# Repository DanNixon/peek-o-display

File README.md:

# Peek-o-Display

The moderately simple coming together of a Pi Pico (compatible) and generic 2.8" display with touch panel and SD card slot.
Designed to be a simple module that can slot onto various pieces of hardware that need a microcontroller and display (and maybe storage).

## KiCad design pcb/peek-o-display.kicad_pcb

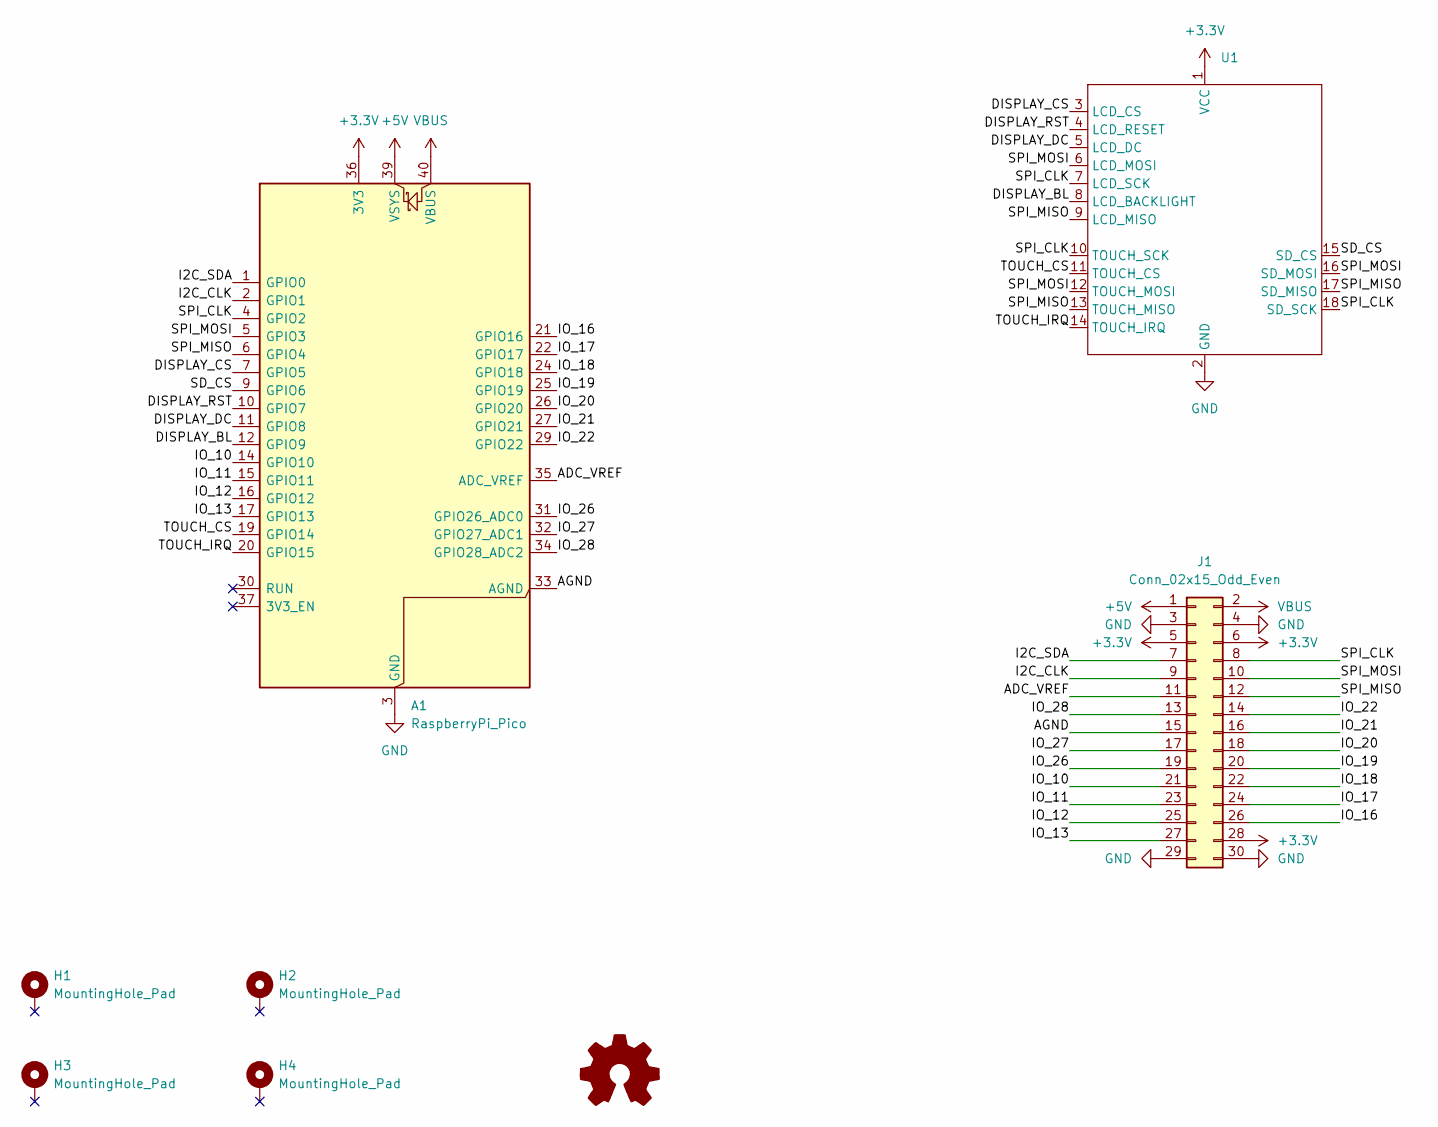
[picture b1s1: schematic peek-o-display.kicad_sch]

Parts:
A1: RaspberryPi_Pico; RaspberryPi_Pico_Common
H1, H2, H3, H4: MountingHole_Pad; MountingHole_3.2mm_M3_Pad_Via
J1: Conn_02x15_Odd_Even; PinSocket_2x15_P2.54mm_Vertical
U1: ILI9341_2.8in_with_touch_and_sd

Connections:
+3.3V: A1.36 (3V3), J1.5, J1.6, J1.28, U1.1 (VCC)
+5V: A1.39 (VSYS), J1.1
/ADC_VREF: A1.35 (ADC_VREF), J1.11
/AGND: A1.33 (AGND), J1.15
/DISPLAY_BL: A1.12 (GPIO9), U1.8 (LCD_BACKLIGHT)
/DISPLAY_CS: A1.7 (GPIO5), U1.3 (LCD_CS)
/DISPLAY_DC: A1.11 (GPIO8), U1.5 (LCD_DC)
/DISPLAY_RST: A1.10 (GPIO7), U1.4 (LCD_RESET)
/I2C_CLK: A1.2 (GPIO1), J1.9
/I2C_SDA: A1.1 (GPIO0), J1.7
/IO_10: A1.14 (GPIO10), J1.21
/IO_11: A1.15 (GPIO11), J1.23
/IO_12: A1.16 (GPIO12), J1.25
/IO_13: A1.17 (GPIO13), J1.27
/IO_16: A1.21 (GPIO16), J1.26
/IO_17: A1.22 (GPIO17), J1.24
/IO_18: A1.24 (GPIO18), J1.22
/IO_19: A1.25 (GPIO19), J1.20
/IO_20: A1.26 (GPIO20), J1.18
/IO_21: A1.27 (GPIO21), J1.16
/IO_22: A1.29 (GPIO22), J1.14
/IO_26: A1.31 (GPIO26_ADC0), J1.19
/IO_27: A1.32 (GPIO27_ADC1), J1.17
/IO_28: A1.34 (GPIO28_ADC2), J1.13
/SD_CS: A1.9 (GPIO6), U1.15 (SD_CS)
/SPI_CLK: A1.4 (GPIO2), J1.8, U1.7 (LCD_SCK), U1.10 (TOUCH_SCK), U1.18 (SD_SCK)
/SPI_MISO: A1.6 (GPIO4), J1.12, U1.9 (LCD_MISO), U1.13 (TOUCH_MISO), U1.17 (SD_MISO)
/SPI_MOSI: A1.5 (GPIO3), J1.10, U1.6 (LCD_MOSI), U1.12 (TOUCH_MOSI), U1.16 (SD_MOSI)
/TOUCH_CS: A1.19 (GPIO14), U1.11 (TOUCH_CS)
/TOUCH_IRQ: A1.20 (GPIO15), U1.14 (TOUCH_IRQ)
GND: A1.3 (GND), A1.8 (GND), A1.13 (GND), A1.18 (GND), A1.23 (GND), A1.28 (GND), A1.38 (GND), J1.3, J1.4, J1.29, J1.30, U1.2 (GND)
VBUS: A1.40 (VBUS), J1.2

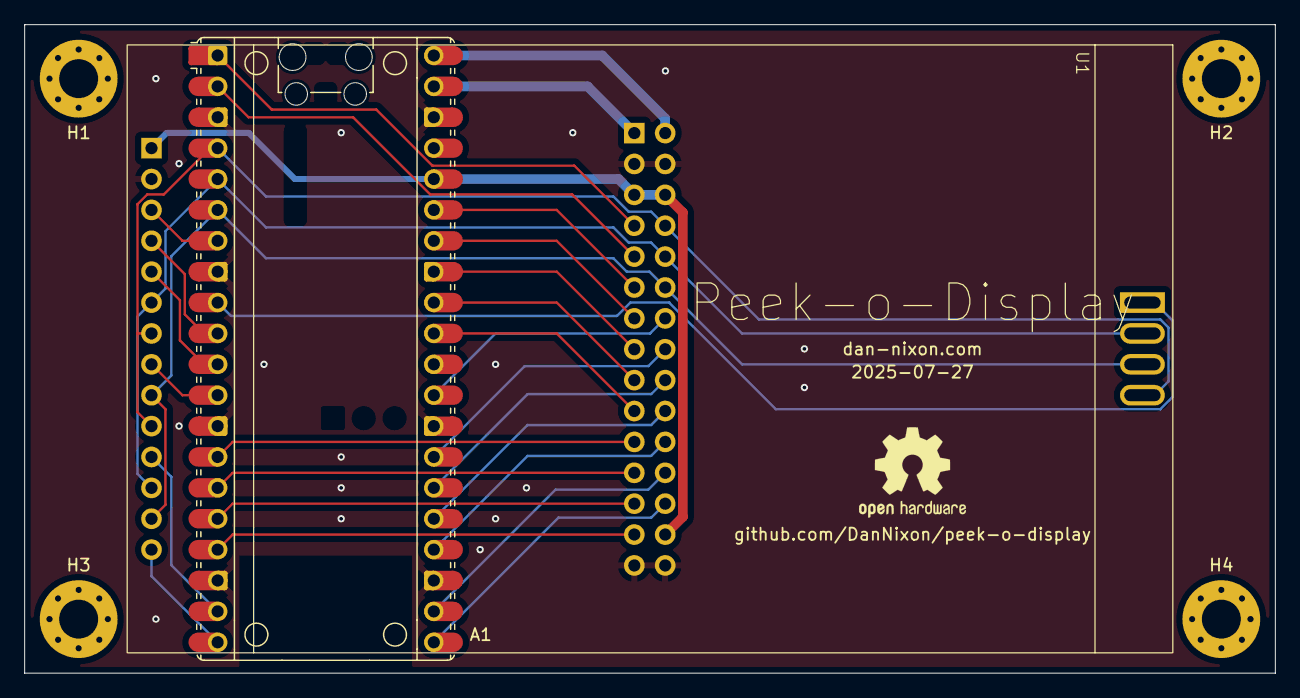
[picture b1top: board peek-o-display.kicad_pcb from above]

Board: 2 copper layers, 102.9 x 53.3 mm, 7 parts (1 on the bottom side), 32 nets.

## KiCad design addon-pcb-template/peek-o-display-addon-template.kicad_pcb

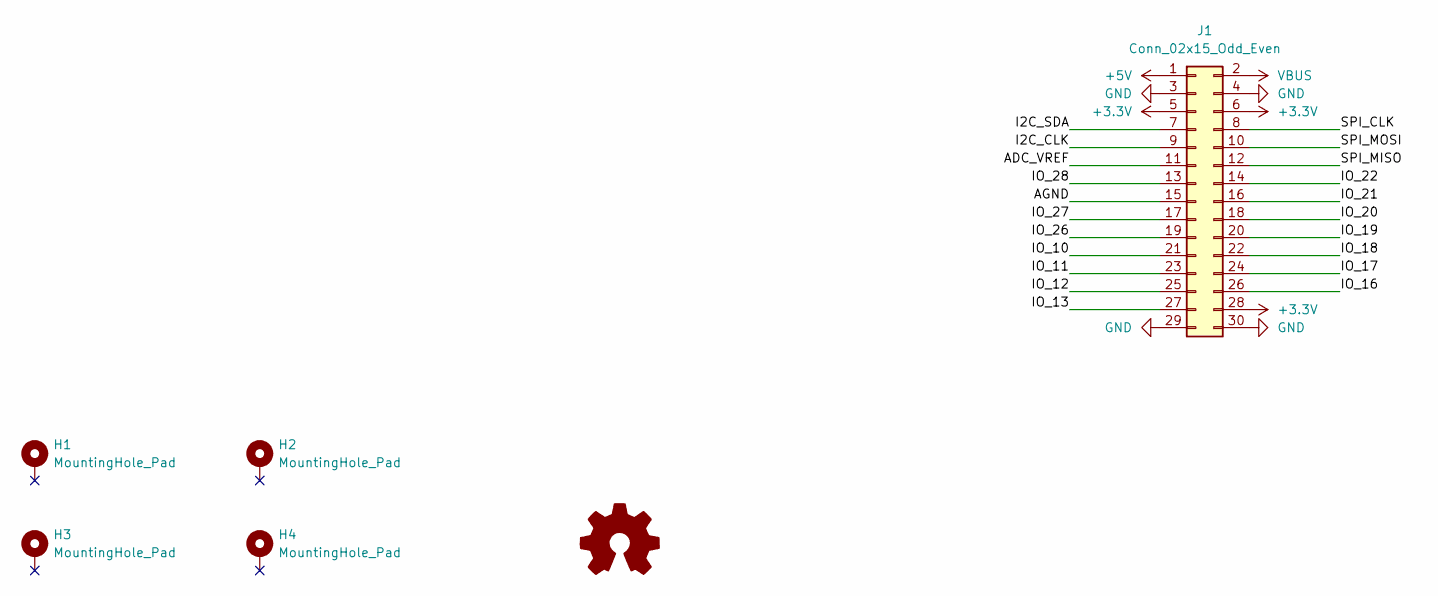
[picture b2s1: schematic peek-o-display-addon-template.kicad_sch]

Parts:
H1, H2, H3, H4: MountingHole_Pad; MountingHole_3.2mm_M3_Pad_Via
J1: Conn_02x15_Odd_Even; PinSocket_2x15_P2.54mm_Vertical

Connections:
+3.3V: J1.5, J1.6, J1.28
+5V: J1.1
/ADC_VREF: J1.11
/AGND: J1.15
/I2C_CLK: J1.9
/I2C_SDA: J1.7
/IO_10: J1.21
/IO_11: J1.23
/IO_12: J1.25
/IO_13: J1.27
/IO_16: J1.26
/IO_17: J1.24
/IO_18: J1.22
/IO_19: J1.20
/IO_20: J1.18
/IO_21: J1.16
/IO_22: J1.14
/IO_26: J1.19
/IO_27: J1.17
/IO_28: J1.13
/SPI_CLK: J1.8
/SPI_MISO: J1.12
/SPI_MOSI: J1.10
GND: J1.3, J1.4, J1.29, J1.30
VBUS: J1.2

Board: 2 copper layers, 5 parts (1 on the bottom side), 2 nets, no tracks yet.

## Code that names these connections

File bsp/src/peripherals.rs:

// Non renamed re-exported peripherals
pub use embassy_rp::peripherals::{
    ADC, ADC_TEMP_SENSOR, BOOTSEL, CORE1, DMA_CH0, DMA_CH1, DMA_CH2, DMA_CH3, DMA_CH4, DMA_CH5,
    DMA_CH6, DMA_CH7, DMA_CH8, DMA_CH9, DMA_CH10, DMA_CH11, FLASH, I2C0, I2C1, PIN_0, PIN_1,
    PIN_10, PIN_11, PIN_12, PIN_13, PIN_16, PIN_17, PIN_18, PIN_19, PIN_20, PIN_21, PIN_22, PIN_23,
    PIN_24, PIN_25, PIN_26, PIN_27, PIN_28, PIN_29, PIN_QSPI_SCLK, PIN_QSPI_SD0, PIN_QSPI_SD1,
    PIN_QSPI_SD2, PIN_QSPI_SD3, PIN_QSPI_SS, PIO0, PIO1, PWM_SLICE0, PWM_SLICE1, PWM_SLICE2,
    PWM_SLICE3, PWM_SLICE4, PWM_SLICE5, PWM_SLICE6, PWM_SLICE7, RTC, SPI0, SPI1, UART0, UART1, USB,
    WATCHDOG,
};

// Non renamed re-exported peripherals
#[cfg(feature = "rp235xa")]
pub use embassy_rp::peripherals::{
    DMA_CH12, DMA_CH13, DMA_CH14, DMA_CH15, PIO2, PWM_SLICE8, PWM_SLICE9, PWM_SLICE10, PWM_SLICE11,
    TRNG,
};

// Renamed pins
pub use embassy_rp::peripherals::{
    PIN_2 as SPI_CLK, PIN_3 as SPI_MOSI, PIN_4 as SPI_MISO, PIN_5 as DISPLAY_CS,
    PIN_6 as SDCARD_CS, PIN_7 as DISPLAY_RESET, PIN_8 as DISPLAY_DC, PIN_9 as DISPLAY_BACKLIGHT,
    PIN_14 as TOUCH_CS, PIN_15 as TOUCH_IRQ,
};

pub use embassy_rp::Peri;

/// Struct containing peripherals, appropriately named for the Peek-o-Display board.
#[allow(non_snake_case)]
pub struct Peripherals {
    pub PIN_0: Peri<'static, PIN_0>,
    pub PIN_1: Peri<'static, PIN_1>,
    pub PIN_10: Peri<'static, PIN_10>,
    pub PIN_11: Peri<'static, PIN_11>,
    pub PIN_12: Peri<'static, PIN_12>,
    pub PIN_13: Peri<'static, PIN_13>,
    pub PIN_16: Peri<'static, PIN_16>,
    pub PIN_17: Peri<'static, PIN_17>,
    pub PIN_18: Peri<'static, PIN_18>,
    pub PIN_19: Peri<'static, PIN_19>,
    pub PIN_20: Peri<'static, PIN_20>,
    pub PIN_21: Peri<'static, PIN_21>,
    pub PIN_22: Peri<'static, PIN_22>,
    pub PIN_23: Peri<'static, PIN_23>,
    pub PIN_24: Peri<'static, PIN_24>,
    pub PIN_25: Peri<'static, PIN_25>,
    pub PIN_26: Peri<'static, PIN_26>,
    pub PIN_27: Peri<'static, PIN_27>,
    pub PIN_28: Peri<'static, PIN_28>,
    pub PIN_29: Peri<'static, PIN_29>,

    pub PIN_QSPI_SCLK: Peri<'static, PIN_QSPI_SCLK>,
    pub PIN_QSPI_SS: Peri<'static, PIN_QSPI_SS>,
    pub PIN_QSPI_SD0: Peri<'static, PIN_QSPI_SD0>,
    pub PIN_QSPI_SD1: Peri<'static, PIN_QSPI_SD1>,
    pub PIN_QSPI_SD2: Peri<'static, PIN_QSPI_SD2>,
    pub PIN_QSPI_SD3: Peri<'static, PIN_QSPI_SD3>,

    pub UART0: Peri<'static, UART0>,
    pub UART1: Peri<'static, UART1>,

    pub SPI1: Peri<'static, SPI1>,

    pub I2C0: Peri<'static, I2C0>,
    pub I2C1: Peri<'static, I2C1>,

    pub DMA_CH0: Peri<'static, DMA_CH0>,
    pub DMA_CH1: Peri<'static, DMA_CH1>,
    pub DMA_CH2: Peri<'static, DMA_CH2>,
    pub DMA_CH3: Peri<'static, DMA_CH3>,
    pub DMA_CH4: Peri<'static, DMA_CH4>,
    pub DMA_CH5: Peri<'static, DMA_CH5>,
    pub DMA_CH6: Peri<'static, DMA_CH6>,
    pub DMA_CH7: Peri<'static, DMA_CH7>,
    pub DMA_CH8: Peri<'static, DMA_CH8>,
    pub DMA_CH9: Peri<'static, DMA_CH9>,
    pub DMA_CH10: Peri<'static, DMA_CH10>,
    pub DMA_CH11: Peri<'static, DMA_CH11>,
    #[cfg(feature = "rp235xa")]
    pub DMA_CH12: Peri<'static, DMA_CH12>,
    #[cfg(feature = "rp235xa")]
    pub DMA_CH13: Peri<'static, DMA_CH13>,
    #[cfg(feature = "rp235xa")]
    pub DMA_CH14: Peri<'static, DMA_CH14>,
    #[cfg(feature = "rp235xa")]
    pub DMA_CH15: Peri<'static, DMA_CH15>,

    pub PWM_SLICE0: Peri<'static, PWM_SLICE0>,
    pub PWM_SLICE1: Peri<'static, PWM_SLICE1>,
    pub PWM_SLICE2: Peri<'static, PWM_SLICE2>,
    pub PWM_SLICE3: Peri<'static, PWM_SLICE3>,
    pub PWM_SLICE4: Peri<'static, PWM_SLICE4>,
    pub PWM_SLICE5: Peri<'static, PWM_SLICE5>,
    pub PWM_SLICE6: Peri<'static, PWM_SLICE6>,
    pub PWM_SLICE7: Peri<'static, PWM_SLICE7>,
    #[cfg(feature = "rp235xa")]
    pub PWM_SLICE8: Peri<'static, PWM_SLICE8>,
    #[cfg(feature = "rp235xa")]
    pub PWM_SLICE9: Peri<'static, PWM_SLICE9>,
    #[cfg(feature = "rp235xa")]
    pub PWM_SLICE10: Peri<'static, PWM_SLICE10>,
    #[cfg(feature = "rp235xa")]
    pub PWM_SLICE11: Peri<'static, PWM_SLICE11>,

    pub USB: Peri<'static, USB>,

    pub RTC: Peri<'static, RTC>,

    pub FLASH: Peri<'static, FLASH>,

    pub ADC: Peri<'static, ADC>,
    pub ADC_TEMP_SENSOR: Peri<'static, ADC_TEMP_SENSOR>,

    pub CORE1: Peri<'static, CORE1>,

    pub PIO0: Peri<'static, PIO0>,
    pub PIO1: Peri<'static, PIO1>,
    #[cfg(feature = "rp235xa")]
    pub PIO2: Peri<'static, PIO2>,

    pub WATCHDOG: Peri<'static, WATCHDOG>,

    pub BOOTSEL: Peri<'static, BOOTSEL>,

    #[cfg(feature = "rp235xa")]
    pub TRNG: Peri<'static, TRNG>,
}

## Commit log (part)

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2025-04-28 pcb: initial version
2025-04-28 bsp: initial version
2025-04-28 bsp: examples
2025-04-28 Update devenv
2025-04-28 bsp: add kitchen sink example for Pico 2
2025-04-28 bsp: add Pico 2 copy of demo firmware
2025-04-28 bsp: tidy examples
2025-04-28 bsp: use in all examples
2025-07-21 bsp: update Rust version
2025-07-22 bsp: finish board peripheral support
2025-07-22 build(deps): update embassy-rp requirement
    Updates the requirements on [embassy-rp](https://github.com/embassy-rs/embassy) to permit the latest version.
    Updates `embassy-rp` to 0.5.0
    - [Changelog](https://github.com/embassy-rs/embassy/blob/main/RELEASE.md)
    - [Commits](https://github.com/embassy-rs/embassy/compare/embassy-rp-v0.4.0...embassy-rp-v0.5.0)
    ---
    updated-dependencies:
2025-07-22 build(deps): bump the cargo-dependencies group
    Updates the requirements on [assign-resources](https://github.com/adamgreig/assign-resources) and [embassy-rp](https://github.com/embassy-rs/embassy) to permit the latest version.
    Updates `assign-resources` to 0.5.0
    - [Changelog](https://github.com/adamgreig/assign-resources/blob/main/CHANGELOG.md)
    - [Commits](https://github.com/adamgreig/assign-resources/compare/v0.4.1...v0.5.0)
    Updates `embassy-rp` to 0.5.0
    - [Changelog](https://github.com/embassy-rs/embassy/blob/main/RELEASE.md)
2025-07-23 Add case template
2025-07-23 Finish touch screen functionality
2025-07-23 build(deps): bump the cargo-dependencies group in /bsp with 4 updates
    Updates the requirements on [embassy-embedded-hal](https://github.com/embassy-rs/embassy), [embassy-rp](https://github.com/embassy-rs/embassy), [embassy-sync](https://github.com/embassy-rs/embassy) a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
    Updates `embassy-embedded-hal` to 0.3.1
    - [Changelog](https://github.com/embassy-rs/embassy/blob/main/RELEASE.md)
    - [Commits](https://github.com/embassy-rs/embassy/compare/embassy-embedded-hal-v0.3.0...embassy-rp-v0.3.1)
    Updates `embassy-rp` to 0.6.0
    - [Changelog](https://github.com/embassy-rs/embassy/blob/main/RELE
2025-07-23 Update Cargo dependencies
2025-07-25 Add addon PCB template
2025-07-27 Slot SD card SPI holes on display module
    Addresses the fact that not all modules seem to have the same distance
    between the two banks of pin headers.
2025-08-01 build(deps): update embassy-executor requirement
    Updates the requirements on [embassy-executor](https://github.com/embassy-rs/embassy) to permit the latest version.
    Updates `embassy-executor` to 0.7.0
    - [Changelog](https://github.com/embassy-rs/embassy/blob/main/RELEASE.md)
    - [Commits](https://github.com/embassy-rs/embassy/compare/embassy-executor-v0.7.0...embassy-executor-v0.7.0)
    ---
    updated-dependencies:
2025-09-02 build(deps): bump the cargo-dependencies group
    Updates the requirements on [embassy-executor](https://github.com/embassy-rs/embassy) and [embassy-time](https://github.com/embassy-rs/embassy) to permit the latest version.
    Updates `embassy-executor` to 0.9.1
    - [Changelog](https://github.com/embassy-rs/embassy/blob/main/RELEASE.md)
    - [Commits](https://github.com/embassy-rs/embassy/compare/embassy-executor-v0.8.0...embassy-executor-v0.9.1)
    Updates `embassy-time` to 0.5.0
    - [Changelog](https://github.com/embassy-rs/embassy/blob/main/RELEASE.md)
2025-09-02 build(deps): bump actions/checkout from 4 to 5
    Bumps [actions/checkout](https://github.com/actions/checkout) from 4 to 5.
    - [Release notes](https://github.com/actions/checkout/releases)
    - [Changelog](https://github.com/actions/checkout/blob/main/CHANGELOG.md)
    - [Commits](https://github.com/actions/checkout/compare/v4...v5)
    ---
    updated-dependencies:
2025-09-07 build(deps): bump the cargo-dependencies group in /bsp with 3 updates
    Updates the requirements on [embassy-embedded-hal](https://github.com/embassy-rs/embassy), [embassy-rp](https://github.com/embassy-rs/embassy) and [embassy-time](https://github.com/embassy-rs/embassy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
    Updates `embassy-embedded-hal` to 0.5.0
    - [Changelog](https://github.com/embassy-rs/embassy/blob/main/RELEASE.md)
    - [Commits](https://github.com/embassy-rs/embassy/compare/embassy-embedded-hal-v0.4.0...embassy-embedded-hal-v0.5.0)
    Updates `embassy-rp` to 0.8.0
    - [Changelog](https://github.com/embassy-rs/embassy/blob/main/RELEASE.md)
2025-12-02 build(deps): update embassy-rp requirement
    Updates the requirements on [embassy-rp](https://github.com/embassy-rs/embassy) to permit the latest version.
    Updates `embassy-rp` to 0.9.0
    - [Changelog](https://github.com/embassy-rs/embassy/blob/main/RELEASE.md)
    - [Commits](https://github.com/embassy-rs/embassy/compare/embassy-rp-v0.8.0...embassy-rp-v0.9.0)
    ---
    updated-dependencies:
2025-12-02 build(deps): bump actions/checkout from 5 to 6
    Bumps [actions/checkout](https://github.com/actions/checkout) from 5 to 6.
    - [Release notes](https://github.com/actions/checkout/releases)
    - [Changelog](https://github.com/actions/checkout/blob/main/CHANGELOG.md)
    - [Commits](https://github.com/actions/checkout/compare/v5...v6)
    ---
    updated-dependencies:
2026-01-13 Switch to flake, update dependabot and Rust version
2026-02-14 Correct a copy-paste mistake
2026-02-14 Use rustup provided rustfmt
2026-02-14 Update flake inputs
2026-04-02 build(deps): bump DeterminateSystems/nix-installer-action from 21 to 22
    Bumps [DeterminateSystems/nix-installer-action](https://github.com/determinatesystems/nix-installer-action) from 21 to 22.
    - [Release notes](https://github.com/determinatesystems/nix-installer-action/releases)
    - [Commits](https://github.com/determinatesystems/nix-installer-action/compare/v21...v22)
    ---
    updated-dependencies:
    - dependency-name: DeterminateSystems/nix-installer-action
2026-04-05 build(deps): bump the cargo-dependencies group across 6 directories with 5 updates
    Updates the requirements on [embassy-embedded-hal](https://github.com/embassy-rs/embassy), [embassy-rp](https://github.com/embassy-rs/embassy), [embassy-sync](https://github.com/embassy-rs/embassy), 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
    Updates `embassy-embedded-hal` to 0.6.0
    - [Changelog](https://github.com/embassy-rs/embassy/blob/main/RELEASE.md)
    - [Commits](https://github.com/embassy-rs/embassy/compare/embassy-embedded-hal-v0.5.0...embassy-embedded-hal-v0.6.0)
    Updates `embassy-rp` to 0.10.0
    - [Changelog](h
